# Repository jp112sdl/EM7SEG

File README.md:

# EM7SEG
electro-mechanical 7 segment display (from dresser/wayne display)
<br/>
_example: use 4 of that nice vintage modules as a clock with a wemos d1 mini, that is getting its time from an ntp service through wifi_

**Teile**
| Ref | Wert | Package | JLCPCB Part |
|--------|--------|--------|--------|
| C1, C2 | 100n | 0805 | C49678 |
| R1-R4,R8-R21 | 10k | 0805 | C17414 |
| R5, R6 | 330 | 0805 | C17630 |
| R7 | 1k | 0805 | C17513 |
| D1, D2 | LED green | 0805 | C2297 |
| D3 | LED red | 0805 | C72038 |
| U2 | MCP23017-E/SS | SSOP | - |
| U3 - U9 | L9110S | TSSOP-8 | - |
| J1, J2 | Pin Header 5x | RM 2.0mm | - |

**Pin Header Zuordnung**
| Pin | Beschreibung |
|--------|--------|
| 1 | GND |
| 2 | Vcc Logik +3.3V / 5V|
| 3 | SDA |
| 4 | SCL |
| 5 | Vcc Segmentspulen 7.5-9V |

## UPDATE 05.03.2020
### Die Platinen sind angekommen 😍
#### ... und ich habe vergessen, einen Motortreiber (U3) bestücken zu lassen 😤 _(aber gut, das ist kein Problem, den MCP23017 muss ich ohnehin noch selbst auflöten)_

## UPDATE 10.04.2020
### Nach einem kleinen Redesign, sind am 09.04.2020 die Platinen V2.0 gekommen,
#### ...die einen Tag später "verarbeitet wurden"
#### Am schwierigsten war der MCP23017 (SSOP) aufzulöten. Von Hand! 

**Ein Mal angefangen, wurden gleich alle Platinen aufgebaut**</br>

**und mit den Displaymodulen "verheiratet"**</br>

## UPDATE 11.04.2020
# Die Uhr läuft!
<br/>

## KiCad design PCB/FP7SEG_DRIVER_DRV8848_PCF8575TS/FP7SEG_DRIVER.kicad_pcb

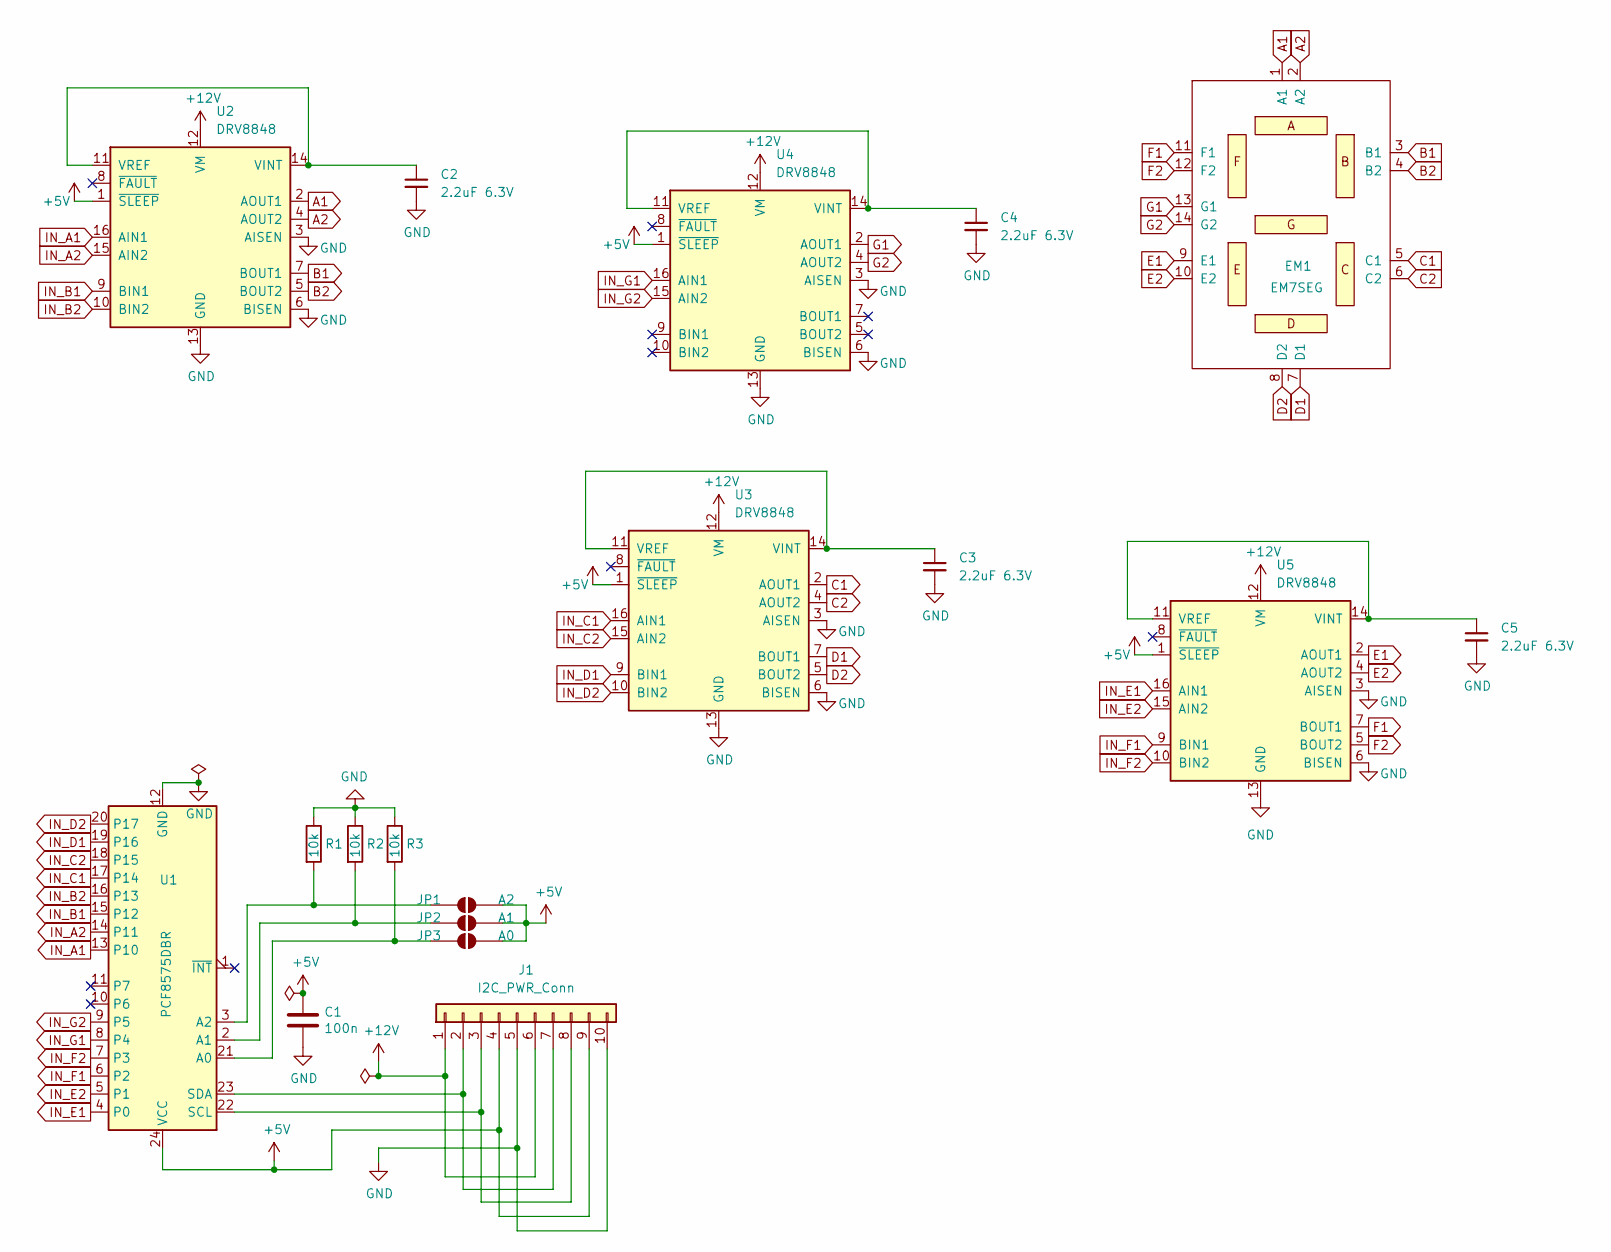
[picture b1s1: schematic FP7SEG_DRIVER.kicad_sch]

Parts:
C1: 100n; C_0805_2012Metric
C2, C3, C4, C5: 2.2uF 6.3V; C_0805_2012Metric
EM1: EM7SEG; FP
J1: I2C_PWR_Conn; PinSocket_1x10_P2.54mm_Vertical
JP1: A2; SolderJumper-2_P1.3mm_Open_RoundedPad1.0x1.5mm
JP2: A1; SolderJumper-2_P1.3mm_Open_RoundedPad1.0x1.5mm
JP3: A0; SolderJumper-2_P1.3mm_Open_RoundedPad1.0x1.5mm
R1, R2, R3: 10k; R_0805_2012Metric
U1: PCF8575DBR; SSOP-24_5.3x8.2mm_P0.65mm
U2, U3, U4, U5: DRV8848; TSSOP-16-1EP_4.4x5mm_P0.65mm

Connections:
+5V: C1.1, J1.4, J1.9, JP1.2 (B), JP2.2 (B), JP3.2 (B), U1.24 (VCC), U2.1 (~SLEEP), U3.1 (~SLEEP), U4.1 (~SLEEP), U5.1 (~SLEEP)
+12V: J1.1, J1.6, U2.12 (VM), U3.12 (VM), U4.12 (VM), U5.12 (VM)
A1: EM1.1 (A1), U2.2 (AOUT1)
A2: EM1.2 (A2), U2.4 (AOUT2)
B1: EM1.3 (B1), U2.7 (BOUT1)
B2: EM1.4 (B2), U2.5 (BOUT2)
C1: EM1.5 (C1), U3.2 (AOUT1)
C2: EM1.6 (C2), U3.4 (AOUT2)
D1: EM1.7 (D1), U3.7 (BOUT1)
D2: EM1.8 (D2), U3.5 (BOUT2)
E1: EM1.9 (E1), U5.2 (AOUT1)
E2: EM1.10 (E2), U5.4 (AOUT2)
F1: EM1.11 (F1), U5.7 (BOUT1)
F2: EM1.12 (F2), U5.5 (BOUT2)
G1: EM1.13 (G1), U4.2 (AOUT1)
G2: EM1.14 (G2), U4.4 (AOUT2)
GND: C1.2, C2.2, C3.2, C4.2, C5.2, J1.5, J1.10, R1.1, R2.1, R3.1, U1.12 (GND), U2.3 (AISEN), U2.6 (BISEN), U2.13 (GND), U2.17 (GND), U3.3 (AISEN), U3.6 (BISEN), U3.13 (GND), U3.17 (GND), U4.3 (AISEN), U4.6 (BISEN), U4.13 (GND), U4.17 (GND), U5.3 (AISEN), U5.6 (BISEN), U5.13 (GND), U5.17 (GND)
IN_A1: U1.13 (P10), U2.16 (AIN1)
IN_A2: U1.14 (P11), U2.15 (AIN2)
IN_B1: U1.15 (P12), U2.9 (BIN1)
IN_B2: U1.16 (P13), U2.10 (BIN2)
IN_C1: U1.17 (P14), U3.16 (AIN1)
IN_C2: U1.18 (P15), U3.15 (AIN2)
IN_D1: U1.19 (P16), U3.9 (BIN1)
IN_D2: U1.20 (P17), U3.10 (BIN2)
IN_E1: U1.4 (P0), U5.16 (AIN1)
IN_E2: U1.5 (P1), U5.15 (AIN2)
IN_F1: U1.6 (P2), U5.9 (BIN1)
IN_F2: U1.7 (P3), U5.10 (BIN2)
IN_G1: U1.8 (P4), U4.16 (AIN1)
IN_G2: U1.9 (P5), U4.15 (AIN2)
unnamed: J1.2, J1.7, U1.23 (SDA)
unnamed: J1.3, J1.8, U1.22 (SCL)
unnamed: JP1.1 (A), R1.2, U1.3 (A2)
unnamed: JP2.1 (A), R2.2, U1.2 (A1)
unnamed: JP3.1 (A), R3.2, U1.21 (A0)
unnamed: C2.1, U2.11 (VREF), U2.14 (VINT)
unnamed: C3.1, U3.11 (VREF), U3.14 (VINT)
unnamed: C4.1, U4.11 (VREF), U4.14 (VINT)
unnamed: C5.1, U5.11 (VREF), U5.14 (VINT)

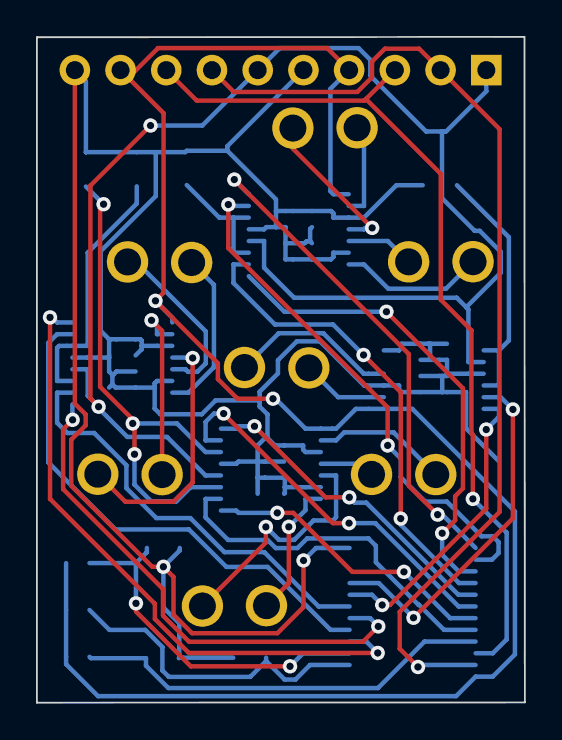
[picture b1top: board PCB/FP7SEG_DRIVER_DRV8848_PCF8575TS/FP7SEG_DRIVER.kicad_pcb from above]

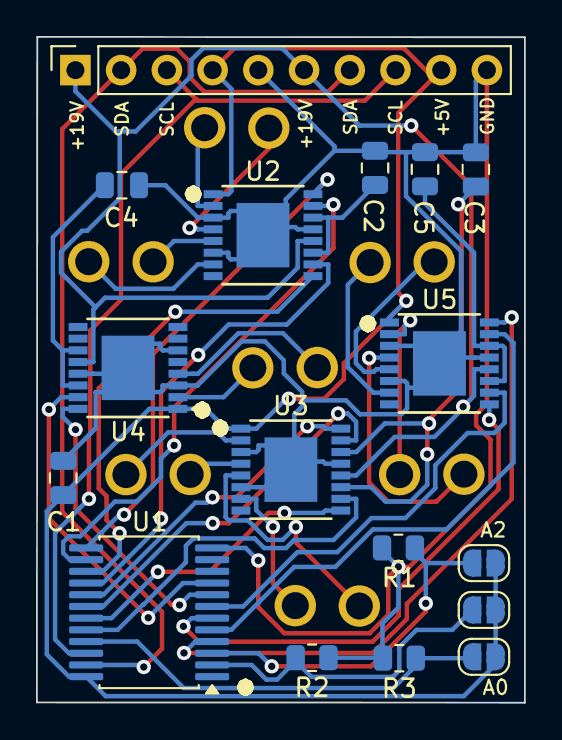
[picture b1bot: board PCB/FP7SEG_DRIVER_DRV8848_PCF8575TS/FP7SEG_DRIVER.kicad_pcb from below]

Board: 2 copper layers, 27.1 x 37.0 mm, 18 parts (17 on the bottom side), 40 nets.

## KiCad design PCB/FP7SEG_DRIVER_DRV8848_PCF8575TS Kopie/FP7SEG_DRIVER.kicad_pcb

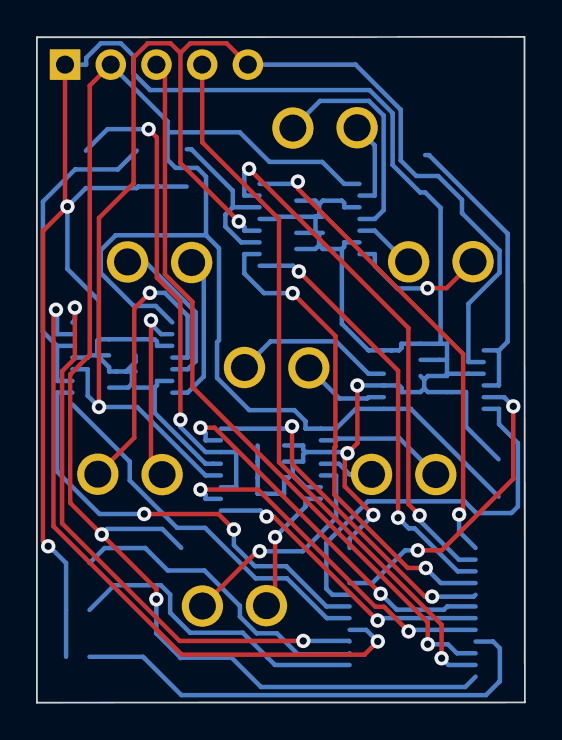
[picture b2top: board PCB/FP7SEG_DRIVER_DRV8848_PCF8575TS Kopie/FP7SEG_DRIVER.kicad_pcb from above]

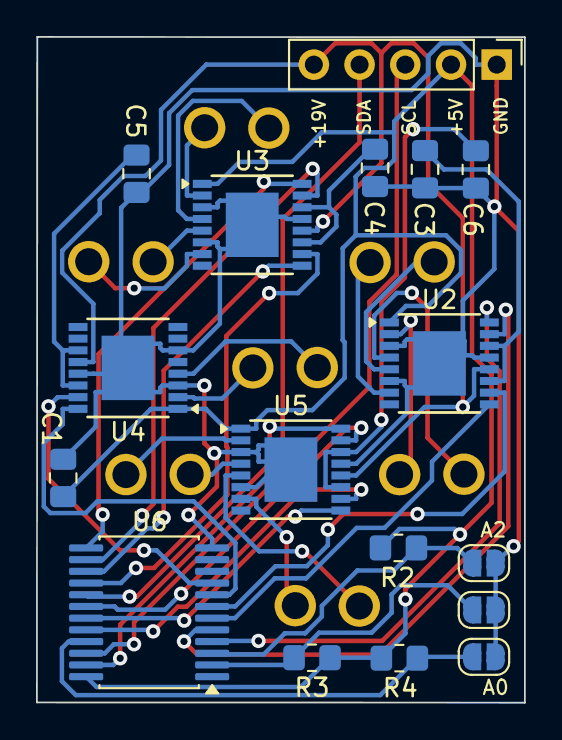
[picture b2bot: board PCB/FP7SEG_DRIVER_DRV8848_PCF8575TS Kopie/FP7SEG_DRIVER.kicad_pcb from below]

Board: 2 copper layers, 27.1 x 37.0 mm, 18 parts (17 on the bottom side), 40 nets.

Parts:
C1: 100n; C_0805_2012Metric_Pad1.18x1.45mm_HandSolder
C3, C4, C5, C6: 2.2uF 6.3V; C_0805_2012Metric_Pad1.18x1.45mm_HandSolder
EM1: EM7SEG; FP
J1: I2C_PWR_IN; PinHeader_1x05_P2.54mm_Vertical
JP1: A0; SolderJumper-2_P1.3mm_Open_RoundedPad1.0x1.5mm
JP2: A1; SolderJumper-2_P1.3mm_Open_RoundedPad1.0x1.5mm
JP3: A2; SolderJumper-2_P1.3mm_Open_RoundedPad1.0x1.5mm
R2, R3, R4: 10k; R_0805_2012Metric_Pad1.20x1.40mm_HandSolder
U2, U3, U4, U5: DRV8848; TSSOP-16-1EP_4.4x5mm_P0.65mm
U6: PCF8575DBR; SSOP-24_5.3x8.2mm_P0.65mm

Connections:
+5V: C1.1, J1.2, R2.1, R3.1, R4.1, U2.1 (~SLEEP), U3.1 (~SLEEP), U4.1 (~SLEEP), U5.1 (~SLEEP), U6.24 (VCC)
+12V: J1.5, U2.12 (VM), U3.12 (VM), U4.12 (VM), U5.12 (VM)
A1: EM1.1 (A1), U3.2 (AOUT1)
A2: EM1.2 (A2), U3.4 (AOUT2)
B1: EM1.3 (B1), U3.7 (BOUT1)
B2: EM1.4 (B2), U3.5 (BOUT2)
C1: EM1.5 (C1), U5.2 (AOUT1)
C2: EM1.6 (C2), U5.4 (AOUT2)
D1: EM1.7 (D1), U5.7 (BOUT1)
D2: EM1.8 (D2), U5.5 (BOUT2)
E1: EM1.9 (E1), U2.2 (AOUT1)
E2: EM1.10 (E2), U2.4 (AOUT2)
F1: EM1.11 (F1), U2.7 (BOUT1)
F2: EM1.12 (F2), U2.5 (BOUT2)
G1: EM1.13 (G1), U4.2 (AOUT1)
G2: EM1.14 (G2), U4.4 (AOUT2)
GND: C1.2, C3.2, C4.2, C5.2, C6.2, J1.1, JP1.2 (B), JP2.2 (B), JP3.2 (B), U2.3 (AISEN), U2.6 (BISEN), U2.13 (GND), U2.17 (GND), U3.3 (AISEN), U3.6 (BISEN), U3.13 (GND), U3.17 (GND), U4.3 (AISEN), U4.6 (BISEN), U4.13 (GND), U4.17 (GND), U5.3 (AISEN), U5.6 (BISEN), U5.13 (GND), U5.17 (GND), U6.12 (GND)
IN_A1: U3.16 (AIN1), U6.13 (P10)
IN_A2: U3.15 (AIN2), U6.14 (P11)
IN_B1: U3.9 (BIN1), U6.15 (P12)
IN_B2: U3.10 (BIN2), U6.16 (P13)
IN_C1: U5.16 (AIN1), U6.17 (P14)
IN_C2: U5.15 (AIN2), U6.18 (P15)
IN_D1: U5.9 (BIN1), U6.19 (P16)
IN_D2: U5.10 (BIN2), U6.20 (P17)
IN_E1: U2.16 (AIN1), U6.4 (P0)
IN_E2: U2.15 (AIN2), U6.5 (P1)
IN_F1: U2.9 (BIN1), U6.6 (P2)
IN_F2: U2.10 (BIN2), U6.7 (P3)
IN_G1: U4.16 (AIN1), U6.8 (P4)
IN_G2: U4.15 (AIN2), U6.9 (P5)
unnamed: J1.3, U6.22 (SCL)
unnamed: J1.4, U6.23 (SDA)
unnamed: JP1.1 (A), R4.2, U6.21 (A0)
unnamed: JP2.1 (A), R3.2, U6.2 (A1)
unnamed: JP3.1 (A), R2.2, U6.3 (A2)
unnamed: C3.1, U2.11 (VREF), U2.14 (VINT)
unnamed: C4.1, U3.11 (VREF), U3.14 (VINT)
unnamed: C5.1, U4.11 (VREF), U4.14 (VINT)
unnamed: C6.1, U5.11 (VREF), U5.14 (VINT)

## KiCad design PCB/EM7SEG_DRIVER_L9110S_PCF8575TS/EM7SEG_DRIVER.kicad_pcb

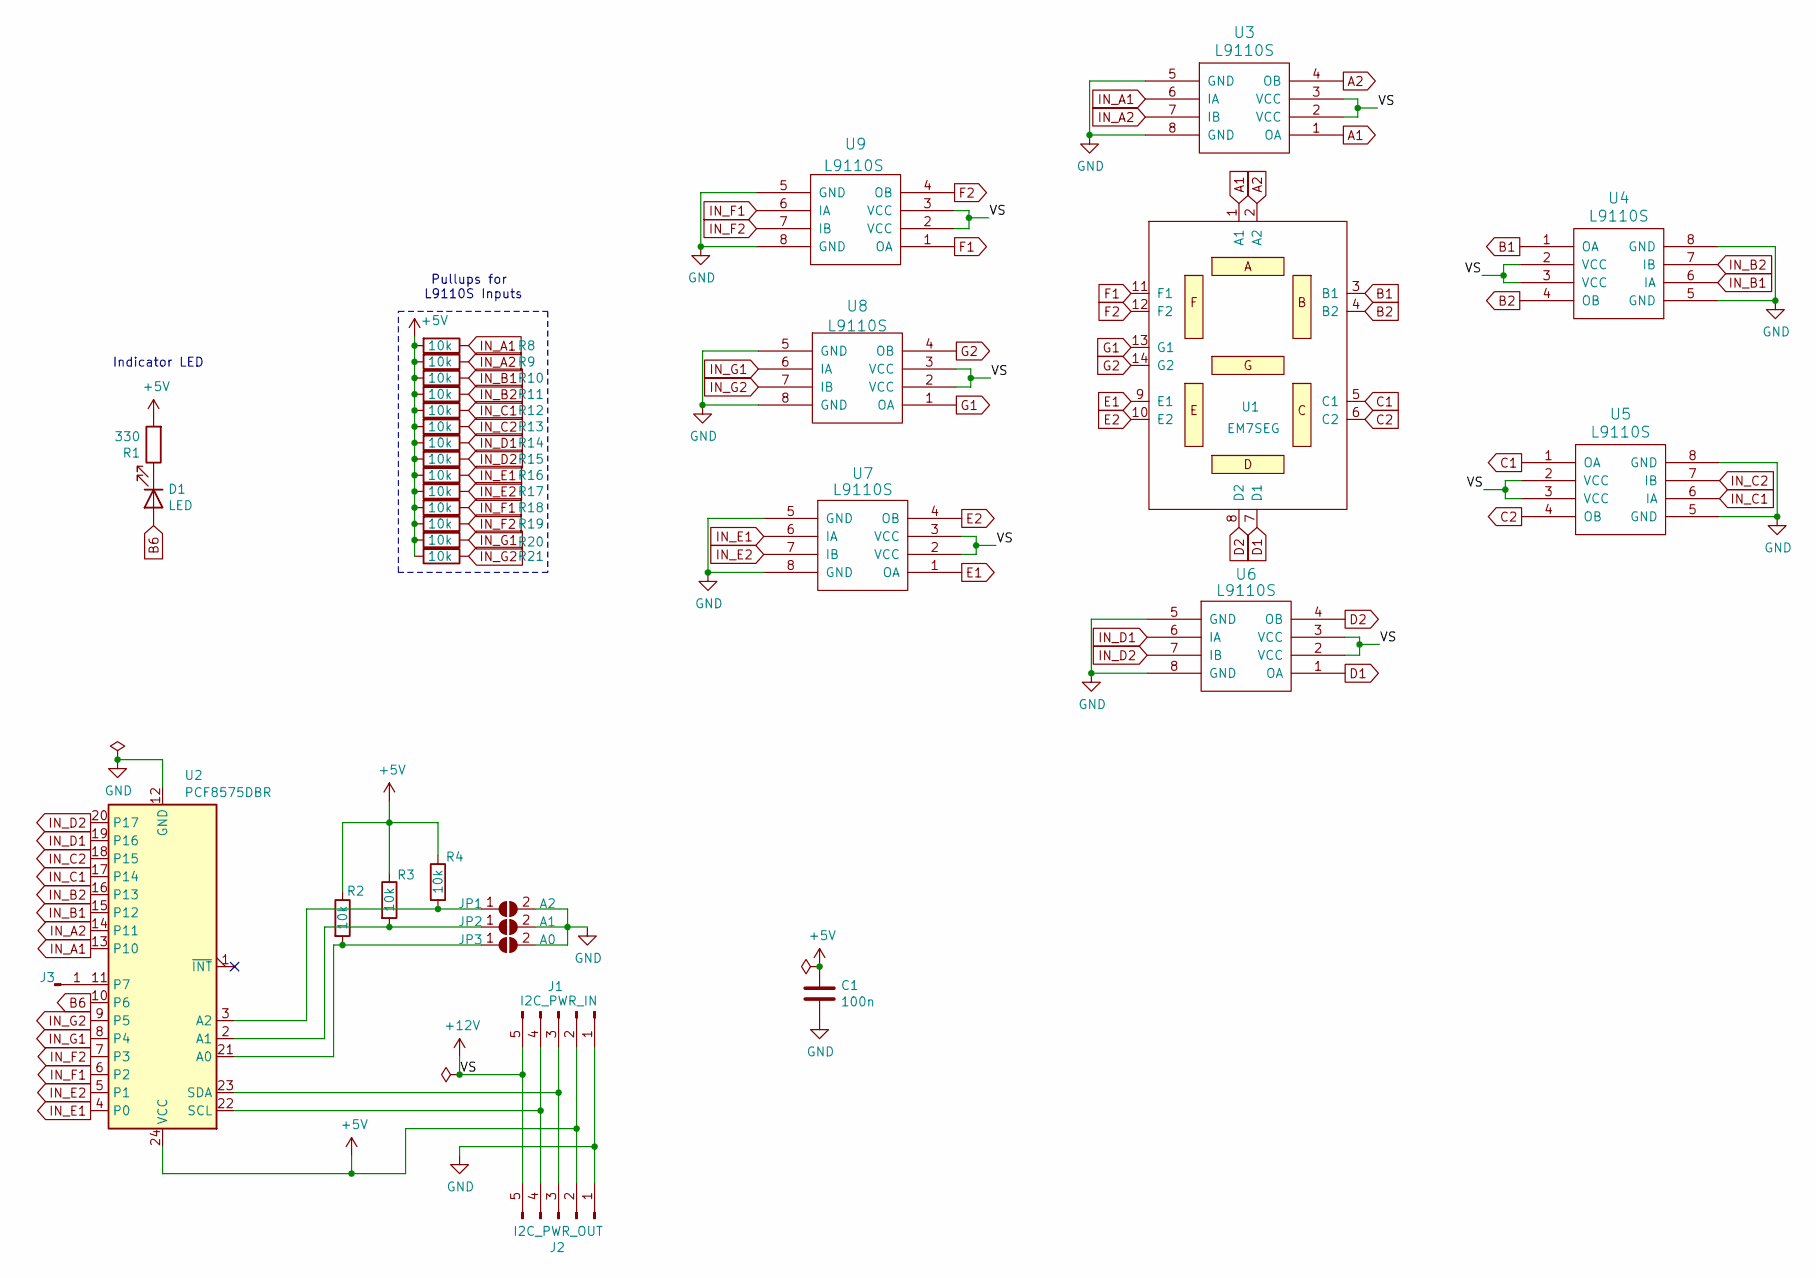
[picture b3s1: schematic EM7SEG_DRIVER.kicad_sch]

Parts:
C1: 100n; C_0805_2012Metric_Pad1.15x1.40mm_HandSolder
D1: LED; LED_0805_2012Metric_Pad1.15x1.40mm_HandSolder
J1: I2C_PWR_IN; PinHeader_1x05_P2.00mm_Vertical
J2: I2C_PWR_OUT; PinHeader_1x05_P2.00mm_Vertical
J3: Pad_IO16; TestPoint_Pad_D1.0mm
JP1: A0; SolderJumper-2_P1.3mm_Open_RoundedPad1.0x1.5mm
JP2: A1; SolderJumper-2_P1.3mm_Open_RoundedPad1.0x1.5mm
JP3: A2; SolderJumper-2_P1.3mm_Open_RoundedPad1.0x1.5mm
R1: 330; R_0805_2012Metric_Pad1.15x1.40mm_HandSolder
R2, R3, R4, R8, R9, R10, R11, R12, R13, R14, R15, R16, R17, R18, R19, R20, R21: 10k; R_0805_2012Metric_Pad1.15x1.40mm_HandSolder
U1: EM7SEG; em7seg
U2: PCF8575DBR; SSOP-24_5.3x8.2mm_P0.65mm
U3, U4, U5, U6, U7, U8, U9: L9110S; SOP-8_3.9x4.9mm_P1.27mm

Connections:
+5V: C1.1, J1.2, J2.2, R1.2, R2.1, R3.1, R4.1, R8.2, R9.2, R10.2, R11.2, R12.2, R13.2, R14.2, R15.2, R16.2, R17.2, R18.2, R19.2, R20.2, R21.2, U2.24 (VCC)
+12V: J1.5, J2.5, U3.2 (VCC), U3.3 (VCC), U4.2 (VCC), U4.3 (VCC), U5.2 (VCC), U5.3 (VCC), U6.2 (VCC), U6.3 (VCC), U7.2 (VCC), U7.3 (VCC), U8.2 (VCC), U8.3 (VCC), U9.2 (VCC), U9.3 (VCC)
A1: U1.1 (A1), U3.1 (OA)
A2: U1.2 (A2), U3.4 (OB)
B1: U1.3 (B1), U4.1 (OA)
B2: U1.4 (B2), U4.4 (OB)
B6: D1.2 (A), U2.10 (P6)
C1: U1.5 (C1), U5.1 (OA)
C2: U1.6 (C2), U5.4 (OB)
D1: U1.7 (D1), U6.1 (OA)
D2: U1.8 (D2), U6.4 (OB)
E1: U1.9 (E1), U7.1 (OA)
E2: U1.10 (E2), U7.4 (OB)
F1: U1.11 (F1), U9.1 (OA)
F2: U1.12 (F2), U9.4 (OB)
G1: U1.13 (G1), U8.1 (OA)
G2: U1.14 (G2), U8.4 (OB)
GND: C1.2, J1.1, J2.1, JP1.2 (B), JP2.2 (B), JP3.2 (B), U2.12 (GND), U3.5 (GND), U3.8 (GND), U4.5 (GND), U4.8 (GND), U5.5 (GND), U5.8 (GND), U6.5 (GND), U6.8 (GND), U7.5 (GND), U7.8 (GND), U8.5 (GND), U8.8 (GND), U9.5 (GND), U9.8 (GND)
IN_A1: R8.1, U2.13 (P10), U3.6 (IA)
IN_A2: R9.1, U2.14 (P11), U3.7 (IB)
IN_B1: R10.1, U2.15 (P12), U4.6 (IA)
IN_B2: R11.1, U2.16 (P13), U4.7 (IB)
IN_C1: R12.1, U2.17 (P14), U5.6 (IA)
IN_C2: R13.1, U2.18 (P15), U5.7 (IB)
IN_D1: R14.1, U2.19 (P16), U6.6 (IA)
IN_D2: R15.1, U2.20 (P17), U6.7 (IB)
IN_E1: R16.1, U2.4 (P0), U7.6 (IA)
IN_E2: R17.1, U2.5 (P1), U7.7 (IB)
IN_F1: R18.1, U2.6 (P2), U9.6 (IA)
IN_F2: R19.1, U2.7 (P3), U9.7 (IB)
IN_G1: R20.1, U2.8 (P4), U8.6 (IA)
IN_G2: R21.1, U2.9 (P5), U8.7 (IB)
unnamed: D1.1 (K), R1.1
unnamed: J1.3, J2.3, U2.23 (SDA)
unnamed: J1.4, J2.4, U2.22 (SCL)
unnamed: J3.1, U2.11 (P7)
unnamed: JP1.1 (A), R4.2, U2.3 (A2)
unnamed: JP2.1 (A), R3.2, U2.2 (A1)
unnamed: JP3.1 (A), R2.2, U2.21 (A0)

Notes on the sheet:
Pullups for L9110S Inputs
Indicator LED

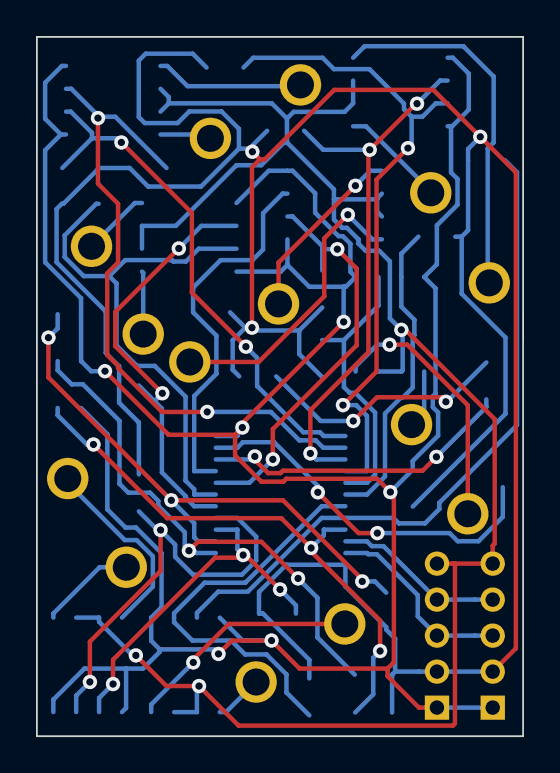
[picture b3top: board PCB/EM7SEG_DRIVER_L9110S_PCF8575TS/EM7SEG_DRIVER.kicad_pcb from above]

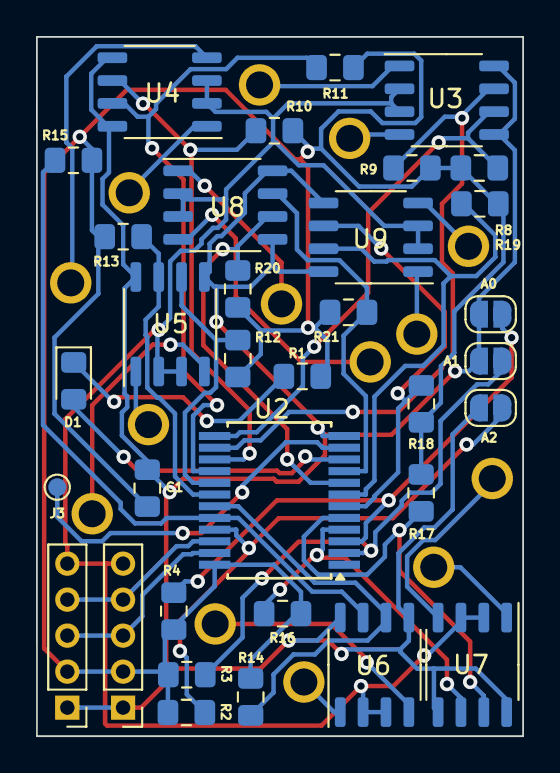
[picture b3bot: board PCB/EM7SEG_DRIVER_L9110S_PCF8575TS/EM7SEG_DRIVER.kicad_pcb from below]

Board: 2 copper layers, 27.0 x 38.8 mm, 35 parts (34 on the bottom side), 39 nets.

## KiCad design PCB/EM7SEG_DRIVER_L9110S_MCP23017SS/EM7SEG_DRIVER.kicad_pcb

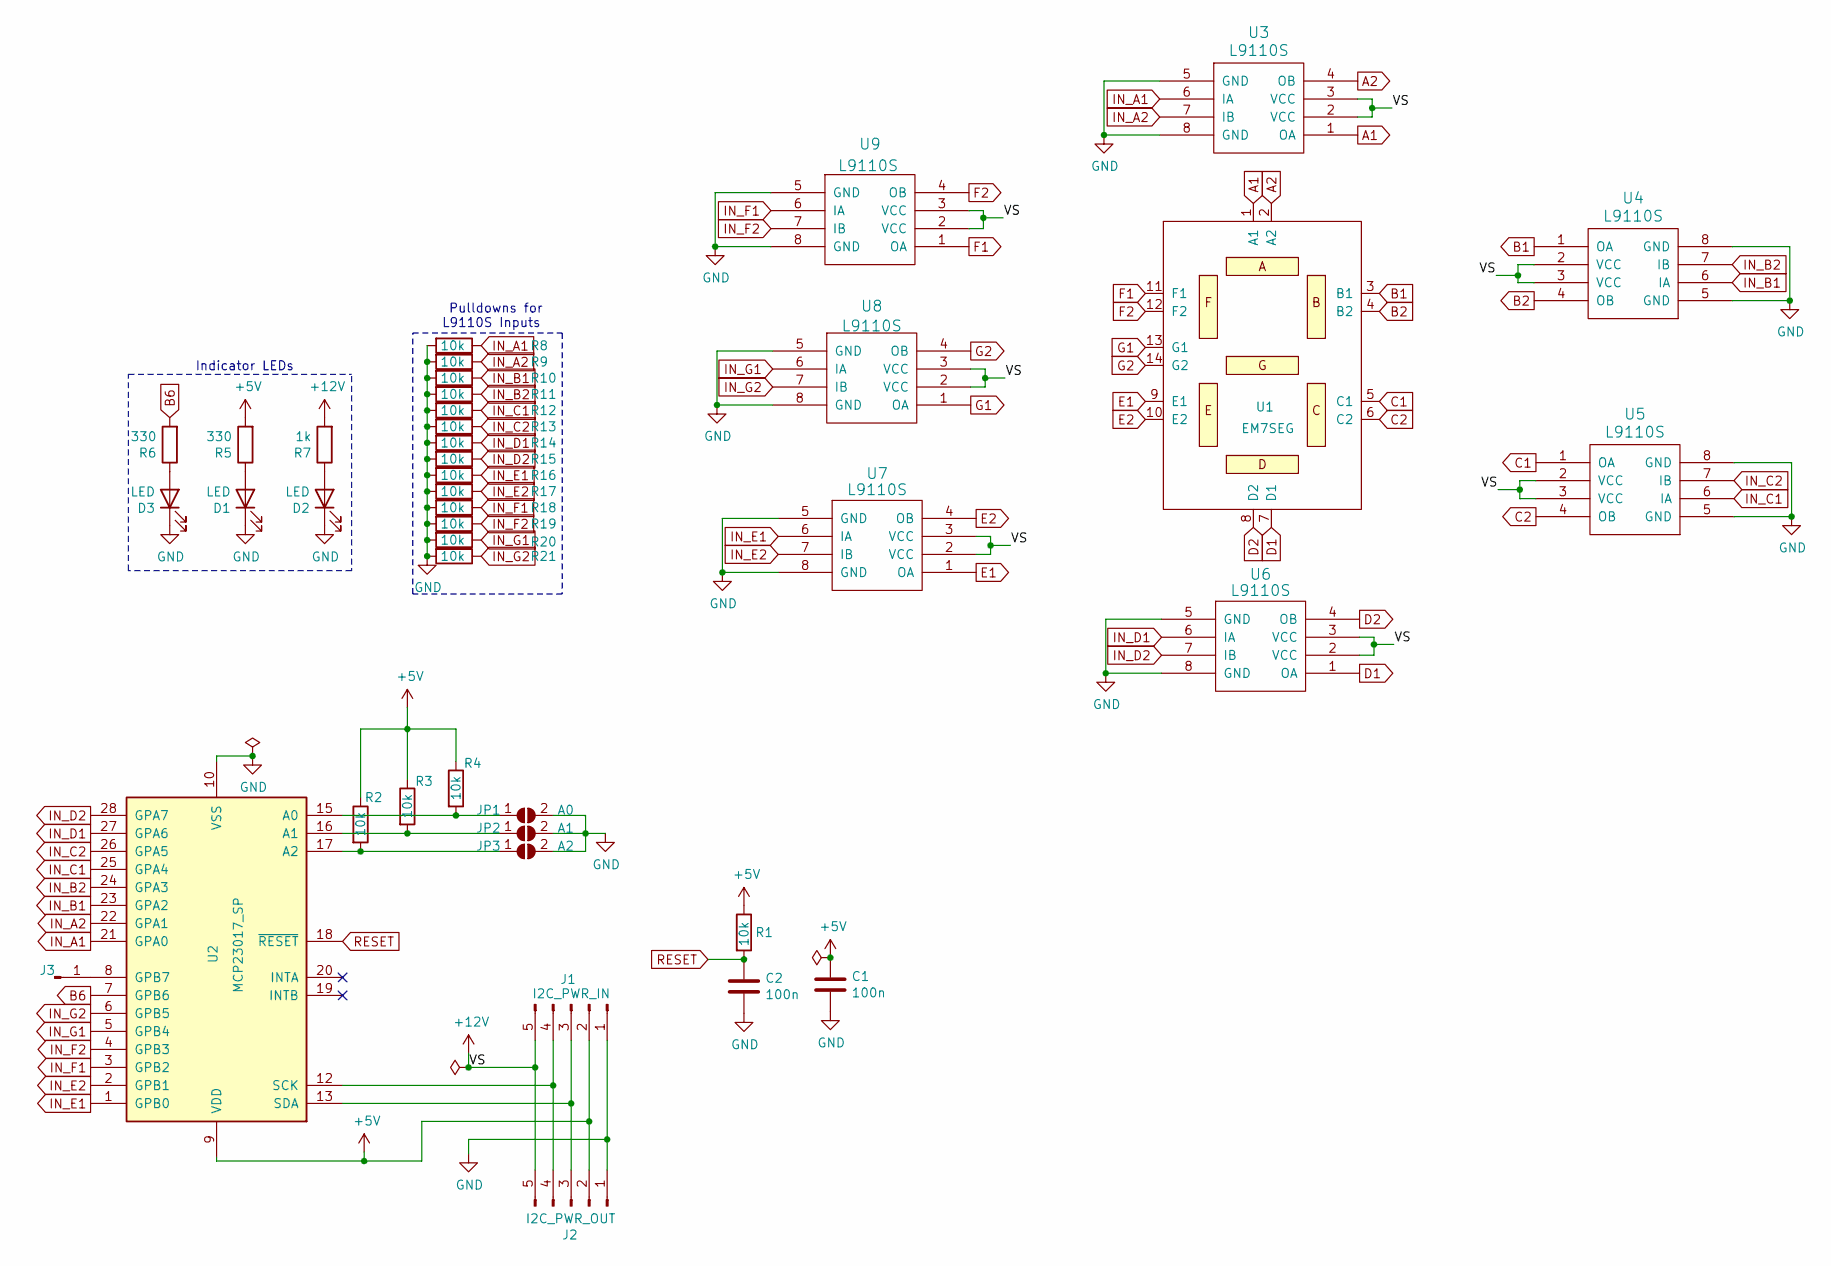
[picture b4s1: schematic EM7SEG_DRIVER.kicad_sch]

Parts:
C1, C2: 100n; C_0805_2012Metric_Pad1.15x1.40mm_HandSolder
D1, D2, D3: LED; LED_0805_2012Metric_Pad1.15x1.40mm_HandSolder
J1: I2C_PWR_IN; PinHeader_1x05_P2.00mm_Vertical
J2: I2C_PWR_OUT; PinHeader_1x05_P2.00mm_Vertical
J3: Pad_IO16; TestPoint_Pad_D1.0mm
JP1: A0; SolderJumper-2_P1.3mm_Open_RoundedPad1.0x1.5mm
JP2: A1; SolderJumper-2_P1.3mm_Open_RoundedPad1.0x1.5mm
JP3: A2; SolderJumper-2_P1.3mm_Open_RoundedPad1.0x1.5mm
R1, R2, R3, R4, R8, R9, R10, R11, R12, R13, R14, R15, R16, R17, R18, R19, R20, R21: 10k; R_0805_2012Metric_Pad1.15x1.40mm_HandSolder
R5, R6: 330; R_0805_2012Metric_Pad1.15x1.40mm_HandSolder
R7: 1k; R_0805_2012Metric_Pad1.15x1.40mm_HandSolder
U1: EM7SEG; em7seg
U2: MCP23017_SP; SSOP-28_5.3x10.2mm_P0.65mm
U3, U4, U5, U6, U7, U8, U9: L9110S; SOP-8_3.9x4.9mm_P1.27mm

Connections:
+5V: C1.1, J1.2, J2.2, R1.1, R2.1, R3.1, R4.1, R5.2, U2.9 (VDD)
+12V: J1.5, J2.5, R7.2, U3.2 (VCC), U3.3 (VCC), U4.2 (VCC), U4.3 (VCC), U5.2 (VCC), U5.3 (VCC), U6.2 (VCC), U6.3 (VCC), U7.2 (VCC), U7.3 (VCC), U8.2 (VCC), U8.3 (VCC), U9.2 (VCC), U9.3 (VCC)
A1: U1.1 (A1), U3.1 (OA)
A2: U1.2 (A2), U3.4 (OB)
B1: U1.3 (B1), U4.1 (OA)
B2: U1.4 (B2), U4.4 (OB)
B6: R6.2, U2.7 (GPB6)
C1: U1.5 (C1), U5.1 (OA)
C2: U1.6 (C2), U5.4 (OB)
D1: U1.7 (D1), U6.1 (OA)
D2: U1.8 (D2), U6.4 (OB)
E1: U1.9 (E1), U7.1 (OA)
E2: U1.10 (E2), U7.4 (OB)
F1: U1.11 (F1), U9.1 (OA)
F2: U1.12 (F2), U9.4 (OB)
G1: U1.13 (G1), U8.1 (OA)
G2: U1.14 (G2), U8.4 (OB)
GND: C1.2, C2.2, D1.1 (K), D2.1 (K), D3.1 (K), J1.1, J2.1, JP1.2 (B), JP2.2 (B), JP3.2 (B), R8.2, R9.2, R10.2, R11.2, R12.2, R13.2, R14.2, R15.2, R16.2, R17.2, R18.2, R19.2, R20.2, R21.2, U2.10 (VSS), U3.5 (GND), U3.8 (GND), U4.5 (GND), U4.8 (GND), U5.5 (GND), U5.8 (GND), U6.5 (GND), U6.8 (GND), U7.5 (GND), U7.8 (GND), U8.5 (GND), U8.8 (GND), U9.5 (GND), U9.8 (GND)
IN_A1: R8.1, U2.21 (GPA0), U3.6 (IA)
IN_A2: R9.1, U2.22 (GPA1), U3.7 (IB)
IN_B1: R10.1, U2.23 (GPA2), U4.6 (IA)
IN_B2: R11.1, U2.24 (GPA3), U4.7 (IB)
IN_C1: R12.1, U2.25 (GPA4), U5.6 (IA)
IN_C2: R13.1, U2.26 (GPA5), U5.7 (IB)
IN_D1: R14.1, U2.27 (GPA6), U6.6 (IA)
IN_D2: R15.1, U2.28 (GPA7), U6.7 (IB)
IN_E1: R16.1, U2.1 (GPB0), U7.6 (IA)
IN_E2: R17.1, U2.2 (GPB1), U7.7 (IB)
IN_F1: R18.1, U2.3 (GPB2), U9.6 (IA)
IN_F2: R19.1, U2.4 (GPB3), U9.7 (IB)
IN_G1: R20.1, U2.5 (GPB4), U8.6 (IA)
IN_G2: R21.1, U2.6 (GPB5), U8.7 (IB)
unnamed: D1.2 (A), R5.1
unnamed: D2.2 (A), R7.1
unnamed: D3.2 (A), R6.1
unnamed: J1.3, J2.3, U2.13 (SDA)
unnamed: J1.4, J2.4, U2.12 (SCK)
unnamed: J3.1, U2.8 (GPB7)
unnamed: JP1.1 (A), R4.2, U2.15 (A0)
unnamed: JP2.1 (A), R3.2, U2.16 (A1)
unnamed: JP3.1 (A), R2.2, U2.17 (A2)
RESET: C2.1, R1.2, U2.18 (~RESET)

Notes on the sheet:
Pulldowns for L9110S Inputs
Indicator LEDs

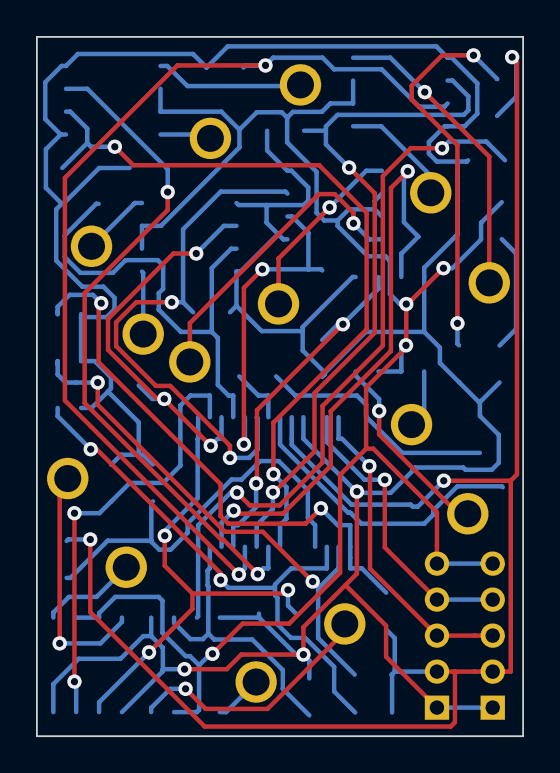
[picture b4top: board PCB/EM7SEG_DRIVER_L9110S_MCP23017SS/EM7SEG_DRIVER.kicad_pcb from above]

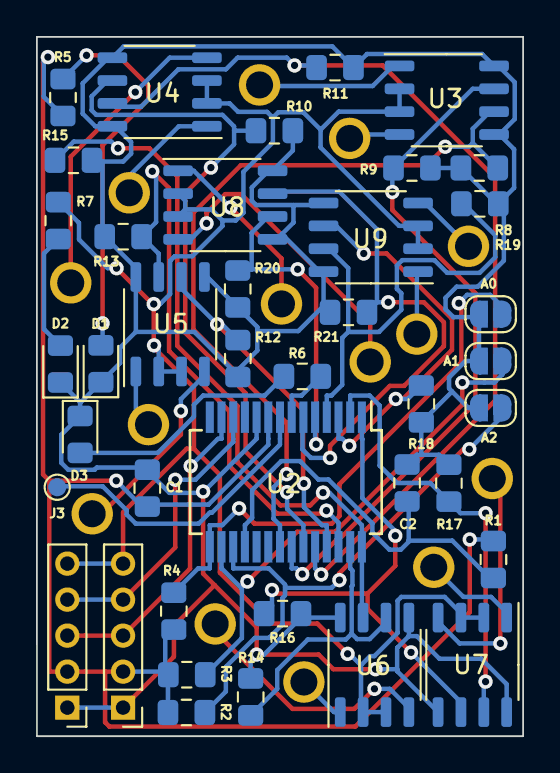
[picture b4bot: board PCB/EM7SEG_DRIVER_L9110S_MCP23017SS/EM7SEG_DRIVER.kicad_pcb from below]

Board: 2 copper layers, 27.0 x 38.8 mm, 41 parts (40 on the bottom side), 42 nets.

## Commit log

2020-02-18 update BOM
2020-02-19 update pcb
2020-02-19 add images
2020-02-19 renamed some types
2020-02-20 add docs
2020-02-20 use pull-downs instead of pull-ups for l9110 inputs
2020-02-20 update gerber
2020-02-21 fix debug
2020-02-21 first dcf77 tests
2020-02-22 update esp8266
2020-04-03 fix parts enumeration
2020-04-11 clock example updated
2020-04-11 add support for some letters/words
2020-04-11 return number of modules in init()
2020-04-11 leading zeros (on/off), alignment (right/left)
2020-04-13 disable indicator led
2020-04-13 switch the modules off/on to strobe a reset
2020-04-13 add delay between segment switches to make smooth animation
2020-05-26 no message
2021-04-09 fixed case
2021-04-09 fix for minute-bug
2022-01-12 update kicad
2024-06-01 update kicad version
2025-05-11 New PCB for PCF8757 IC
2025-05-11 Update project env
2025-05-11 update project files
2026-05-13 update gitignore
2026-05-16 update Em7seg_cntrl.h to make it more generic
